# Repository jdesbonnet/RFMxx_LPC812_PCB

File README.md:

# RFM69HW and RFM98W experimentation board with option for LPC812/LPC824 MCU

This is a PCB board to experiment with HopeRF RFM69HW and RFM98 radio modules (or any modules in that family with a compatible footprint). 

The module can be accessed directly throught JP1 which breaks out the modules SPI bus and a few other pins.

Alternatively a LPC812 (ARM Cortex-M0+ MCU) can be soldered on the board as a controller. Firmware for the LPC812 is here: https://github.com/jdesbonnet/RFM69_LPC812_firmware

There is a blog post discussing this in more detail here: 
http://jdesbonnet.blogspot.ie/2014/12/experiments-with-rfm69-433mhz-digital.html

# Pinout

## Common to RFM69 and RFM98 boards

Leftmost column of 6 pins (from top to bottom): RESET, UART_TXD, UART_RXD, NC, ISP_ENTRY, GND.

Second column from left of 3 pins (from top to bottom): SWD_CLOCK, SWD_DATA, NC.

## RFM69
Three pin row above MCU (from left to right): 3.3V, GND, NC.

## RFM98 
Three pin row at top-right corner of the board (from left to right):  3.3V, GND, NC.

NC: not connect. SWD: serial wire debug. 

# Lessons from first iteration of PCB
 * Keep spacing of headers and test pads snapped to 0.1in grid to facilitate easy construction of bed of nails test rig on proto board.
 * Include power and ground on all headers even if it duplicates.
 * For traces that may become optional use 0 ohm jumper resistors to complete link, or use test pads to allow easy reconnection if a trace needs to be cut (undoing a manually cut trace is a pain).
 * Choice of font on v1 board was too small.
 * Consider side SMA connector
 
 # Version 2 PCB using LPC824

[Version 2 project files](./RFM98LPC824)

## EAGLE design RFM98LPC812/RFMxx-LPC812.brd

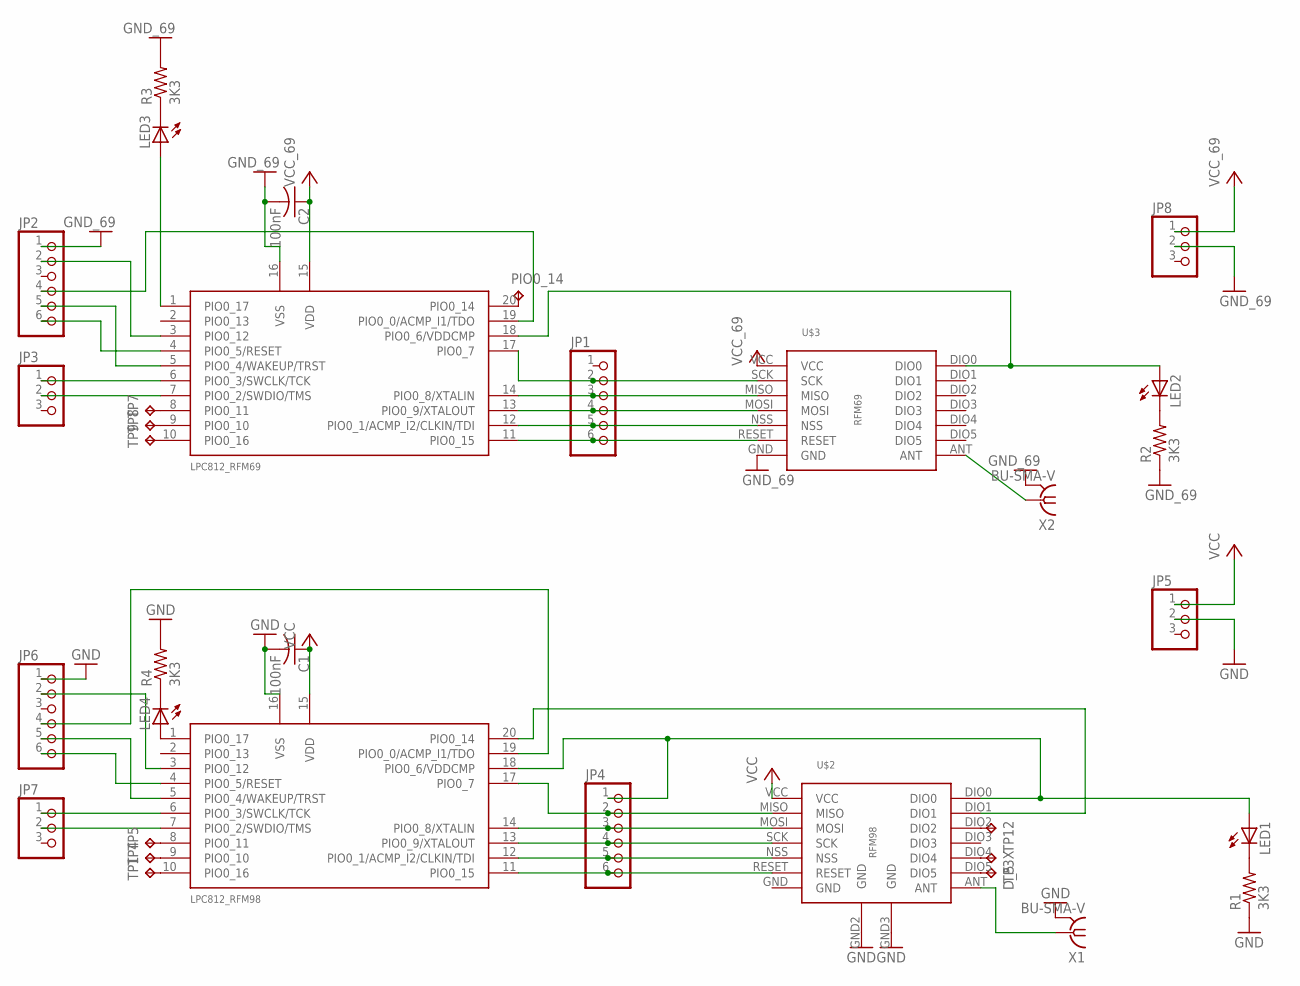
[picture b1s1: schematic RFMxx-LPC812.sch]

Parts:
C1, C2: 100nF; C0805
D_5: TPB1,27; B1,27
JP1, JP2, JP4, JP6: PINHD-1X6; 1X06
JP3, JP5, JP7, JP8: PINHD-1X3; 1X03
LED1, LED2, LED3, LED4: LEDCHIP-LED0805; CHIP-LED0805
LPC812_RFM69, LPC812_RFM98: LPC812M101JD20; SOIC20
PIO0_14: TPB1,27; B1,27
R1, R2, R3, R4: 3K3; R0805
TP1, TP3X, TP4, TP5, TP7, TP8, TP9, TP12: TPB1,27; B1,27
U$2: RFM98W; RFM98_PADS
U$3: RFM69HW; RFM69_PADS
X1, X2: BU-SMA-V

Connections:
GND: C1.2, C2.2, JP2.1, JP5.2, JP6.1, JP8.2, LPC812_RFM69.16 (VSS), LPC812_RFM98.16 (VSS), R1.1, R2.1, R3.2, R4.2, U$2.GND2 (GND), U$2.GND3 (GND), U$3.GND, X1.2, X1.3 (2), X1.4 (2), X1.5 (2), X2.2, X2.3 (2), X2.4 (2), X2.5 (2)
unnamed: U$3.ANT, X2.1
unnamed: JP2.5, LPC812_RFM69.5 (PIO0_4/WAKEUP/TRST)
unnamed: JP3.1, LPC812_RFM69.6 (PIO0_3/SWCLK/TCK)
unnamed: JP2.2, LPC812_RFM69.3 (PIO0_12)
unnamed: JP2.6, LPC812_RFM69.4 (PIO0_5/RESET)
unnamed: U$2.ANT, X1.1
unnamed: JP4.5, LPC812_RFM98.12 (PIO0_1/ACMP_I2/CLKIN/TDI), U$2.NSS
unnamed: JP4.3, LPC812_RFM98.14 (PIO0_8/XTALIN), U$2.MOSI
unnamed: JP4.4, LPC812_RFM98.13 (PIO0_9/XTALOUT), U$2.SCK
unnamed: JP4.2, LPC812_RFM98.17 (PIO0_7), U$2.MISO
unnamed: JP4.6, LPC812_RFM98.11 (PIO0_15), U$2.RESET
unnamed: JP1.6, LPC812_RFM69.11 (PIO0_15), U$3.RESET
unnamed: JP1.5, LPC812_RFM69.12 (PIO0_1/ACMP_I2/CLKIN/TDI), U$3.NSS
unnamed: JP1.4, LPC812_RFM69.13 (PIO0_9/XTALOUT), U$3.MOSI
unnamed: JP1.3, LPC812_RFM69.14 (PIO0_8/XTALIN), U$3.MISO
unnamed: JP6.6, LPC812_RFM98.4 (PIO0_5/RESET)
unnamed: JP6.5, LPC812_RFM98.5 (PIO0_4/WAKEUP/TRST)
unnamed: JP1.2, LPC812_RFM69.17 (PIO0_7), U$3.SCK
unnamed: JP6.4, LPC812_RFM98.19 (PIO0_0/ACMP_I1/TDO)
unnamed: JP6.2, LPC812_RFM98.3 (PIO0_12)
unnamed: JP4.1, LED1.A, LPC812_RFM98.18 (PIO0_6/VDDCMP), U$2.DIO0
unnamed: JP3.2, LPC812_RFM69.7 (PIO0_2/SWDIO/TMS)
unnamed: LED2.A, LPC812_RFM69.18 (PIO0_6/VDDCMP), U$3.DIO0
unnamed: LPC812_RFM98.10 (PIO0_16), TP1.TP
unnamed: LED4.A, LPC812_RFM98.1 (PIO0_17)
unnamed: LPC812_RFM98.20 (PIO0_14), U$2.DIO1
unnamed: JP7.1, LPC812_RFM98.6 (PIO0_3/SWCLK/TCK)
unnamed: JP7.2, LPC812_RFM98.7 (PIO0_2/SWDIO/TMS)
unnamed: TP3X.TP, U$2.DIO4
unnamed: LPC812_RFM98.9 (PIO0_10), TP4.TP
unnamed: LPC812_RFM98.8 (PIO0_11), TP5.TP
unnamed: D_5.TP, U$2.DIO5
unnamed: JP2.4, LPC812_RFM69.19 (PIO0_0/ACMP_I1/TDO)
unnamed: LED3.A, LPC812_RFM69.1 (PIO0_17)
unnamed: LED1.C, R1.2
unnamed: LED2.C, R2.2
unnamed: LED3.C, R3.1
unnamed: LPC812_RFM69.8 (PIO0_11), TP7.TP
unnamed: LED4.C, R4.1
unnamed: LPC812_RFM69.9 (PIO0_10), TP8.TP
unnamed: LPC812_RFM69.10 (PIO0_16), TP9.TP
unnamed: LPC812_RFM69.20 (PIO0_14), PIO0_14.TP
unnamed: TP12.TP, U$2.DIO2
VCC: C1.1, C2.1, JP5.1, JP8.1, LPC812_RFM69.15 (VDD), LPC812_RFM98.15 (VDD), U$2.VCC, U$3.VCC

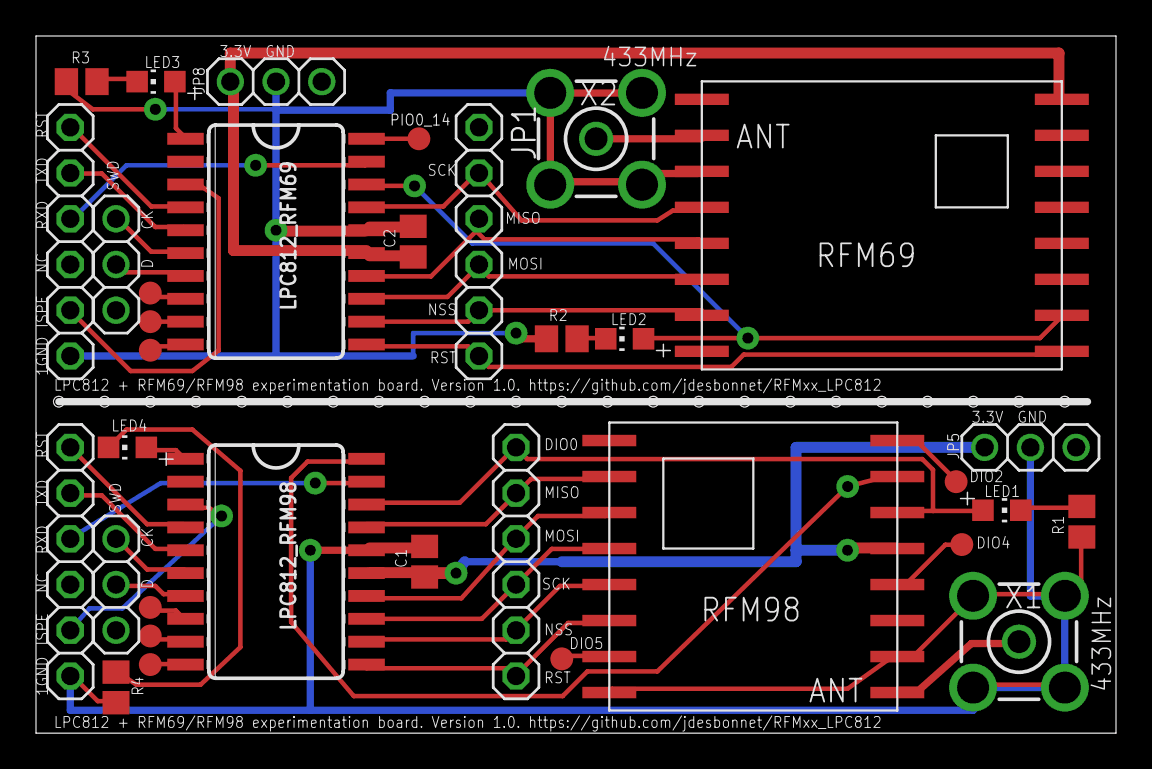
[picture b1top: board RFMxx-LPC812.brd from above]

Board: 2 copper layers, 60.0 x 38.7 mm, 34 parts (0 on the bottom side), 45 nets.

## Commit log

2014-11-03 RFM98W done
2014-11-03 Add RFM69HW device
2014-11-04 move some pins around on RFM69
2014-11-04 first commit of RFMxx board
2014-11-04 no comment
2014-11-05 reasonably good layout on RFM98 side
2014-11-05 start working on RFM69
2014-11-05 start removing ground plane on RFM98 side
2014-11-06 LEDs on DIO0
2014-11-06 trace bug fixes
2014-11-06 attempting to separate vcc, gnd on both sides of the board
2014-11-06 getting close to done
2014-11-07 fixed inconsistency by hand editing .brd XML
2014-11-07 added TPs for DIO0..5 on RFM69 side
2014-11-07 better routing of power to RFM98
2014-11-07 some refinements
2014-11-07 some tidyup before Rev 1
2014-11-07 Remove markings from bottom of board. Failed to reduce quote, so must be the TPs.
2014-11-08 Removed TPs, now quote back down to the EUR 85 level.
2014-11-08 fix some clearance issues which is pushing up the price due to using thinner copper foil
2014-11-08 increase dia of vias: this finally brings the Eurocircuits quote back down to the same level as an earlier version of the board.
2014-11-08 cosmetic changes to board lables
2014-11-08 label cosmetic changes
2014-11-08 more cosmetic changes
2014-11-08 extra holes on dividing line
2014-11-16 Via between RXD on UART connector to PIO0_0 was too close to 3.3V line and merged in V1 of PCB. Move via.
2016-04-24 photo of populated RFM69HW board
2016-08-14 add PCB layout image
2016-08-14 add pinout info
2016-08-14 add image of schematic
2018-04-14 v2.0.0 schematic and layout
2018-04-14 lib files
2018-04-14 move SPI flash MISO trace away from MOSI
2018-04-15 gerber file sent to OSHPark
2018-04-15 add README.md
2018-04-15 add missing RFM_CS trace
2018-04-15 add GPIO11 test pad
2018-04-15 RFM9x breakout
2018-04-15 move RFM9x_breakout to separate github repo
2018-04-15 hand solder friendly pads (extended length)
2018-04-15 LPC824/RFM9x board v2.0.1
2018-04-19 RFM9x compact board
2018-05-13 add 3D rendering
2018-10-16 Add J3, J4 programming header pinout
2018-11-11 kicad 6.0
2018-11-11 schematic
